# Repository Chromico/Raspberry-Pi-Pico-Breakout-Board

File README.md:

# Raspberry Pi Pico Breakout Board

The raspberry pi pico breakout board enables you to use the raspberry pico without having to use a breadboard. The pin headers give you access to the raspberry pi pico pins which can facilitate debugging , making connections using dupont cables and making more permanent connections while keeping the pico board intact.  There is also a reset switch that you can use to reset the raspberry pi pico.

My website: https://tecknologg.website

Blog post: coming soon

# Assembled board

# Documentation
You can get the official documentation here: https://github.com/Chromico/Raspberry-Pi-Pico-Breakout-Board/blob/main/documentation/Raspberry%20Pi%20Pico%20Breakout%20Board%20Documentation.pdf

# Certification
Pending

# Contact

Need to contact me ? Just send me an email at nathan@tecknologg.website or tecknologg@gmail.com

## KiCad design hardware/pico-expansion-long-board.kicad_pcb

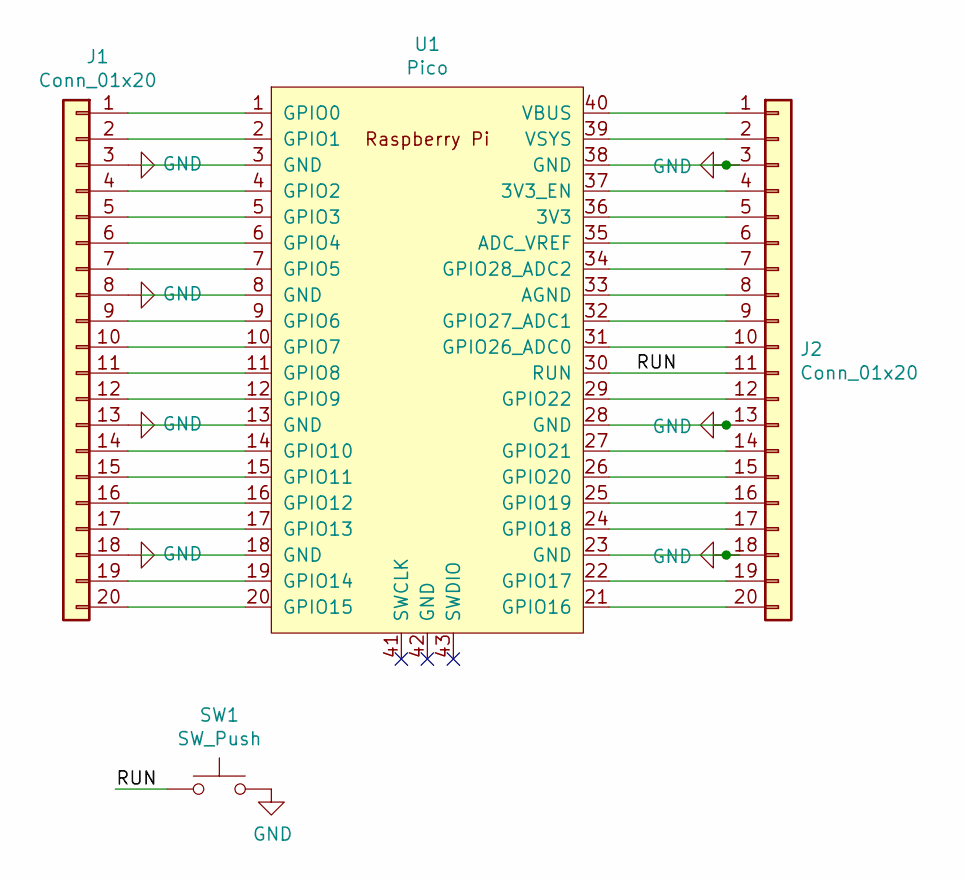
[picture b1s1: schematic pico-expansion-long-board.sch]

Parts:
J1, J2: Conn_01x20
SW1: SW_Push
U1: Pico; RPi_Pico_SMD_TH

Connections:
/RUN: J2.11, SW1.1, U1.30 (RUN)
GND: J1.3, J1.8, J1.13, J1.18, J2.3, J2.13, J2.18, SW1.2, U1.23 (GND), U1.28 (GND), U1.38 (GND)
unnamed: J1.1, U1.1 (GPIO0)
unnamed: J1.2, U1.2 (GPIO1)
unnamed: J1.4, U1.4 (GPIO2)
unnamed: J1.5, U1.5 (GPIO3)
unnamed: J1.6, U1.6 (GPIO4)
unnamed: J1.7, U1.7 (GPIO5)
unnamed: J1.9, U1.9 (GPIO6)
unnamed: J1.10, U1.10 (GPIO7)
unnamed: J1.11, U1.11 (GPIO8)
unnamed: J1.12, U1.12 (GPIO9)
unnamed: J1.14, U1.14 (GPIO10)
unnamed: J1.15, U1.15 (GPIO11)
unnamed: J1.16, U1.16 (GPIO12)
unnamed: J1.17, U1.17 (GPIO13)
unnamed: J1.19, U1.19 (GPIO14)
unnamed: J1.20, U1.20 (GPIO15)
unnamed: J2.1, U1.40 (VBUS)
unnamed: J2.2, U1.39 (VSYS)
unnamed: J2.4, U1.37 (3V3_EN)
unnamed: J2.5, U1.36 (3V3)
unnamed: J2.6, U1.35 (ADC_VREF)
unnamed: J2.7, U1.34 (GPIO28_ADC2)
unnamed: J2.8, U1.33 (AGND)
unnamed: J2.9, U1.32 (GPIO27_ADC1)
unnamed: J2.10, U1.31 (GPIO26_ADC0)
unnamed: J2.12, U1.29 (GPIO22)
unnamed: J2.14, U1.27 (GPIO21)
unnamed: J2.15, U1.26 (GPIO20)
unnamed: J2.16, U1.25 (GPIO19)
unnamed: J2.17, U1.24 (GPIO18)
unnamed: J2.19, U1.22 (GPIO17)
unnamed: J2.20, U1.21 (GPIO16)

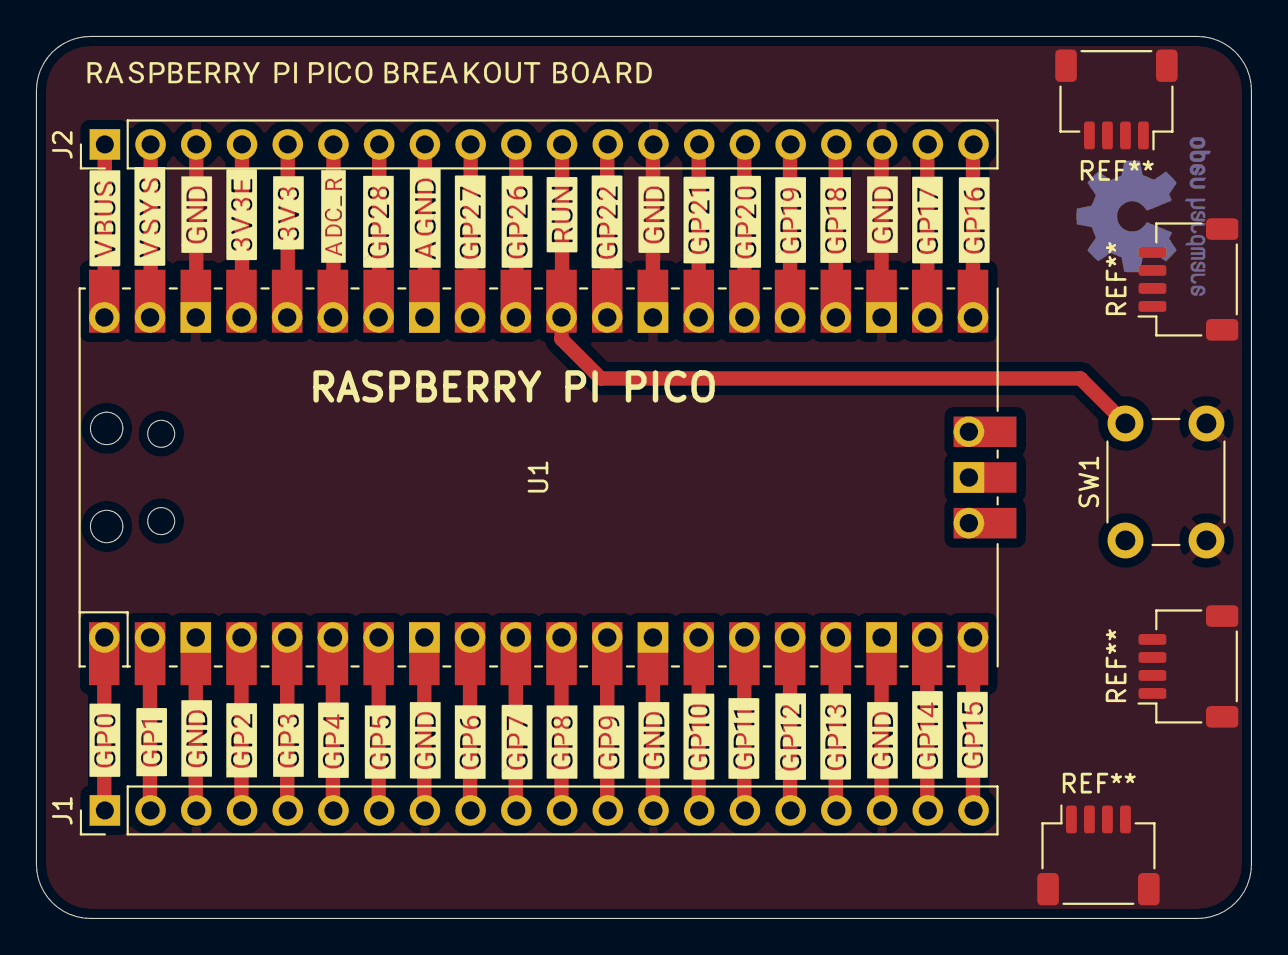
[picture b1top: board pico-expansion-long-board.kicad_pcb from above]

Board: 2 copper layers, 67.5 x 49.0 mm, 4 parts (0 on the bottom side), 34 nets.

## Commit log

2021-07-27 Create LICENSE
